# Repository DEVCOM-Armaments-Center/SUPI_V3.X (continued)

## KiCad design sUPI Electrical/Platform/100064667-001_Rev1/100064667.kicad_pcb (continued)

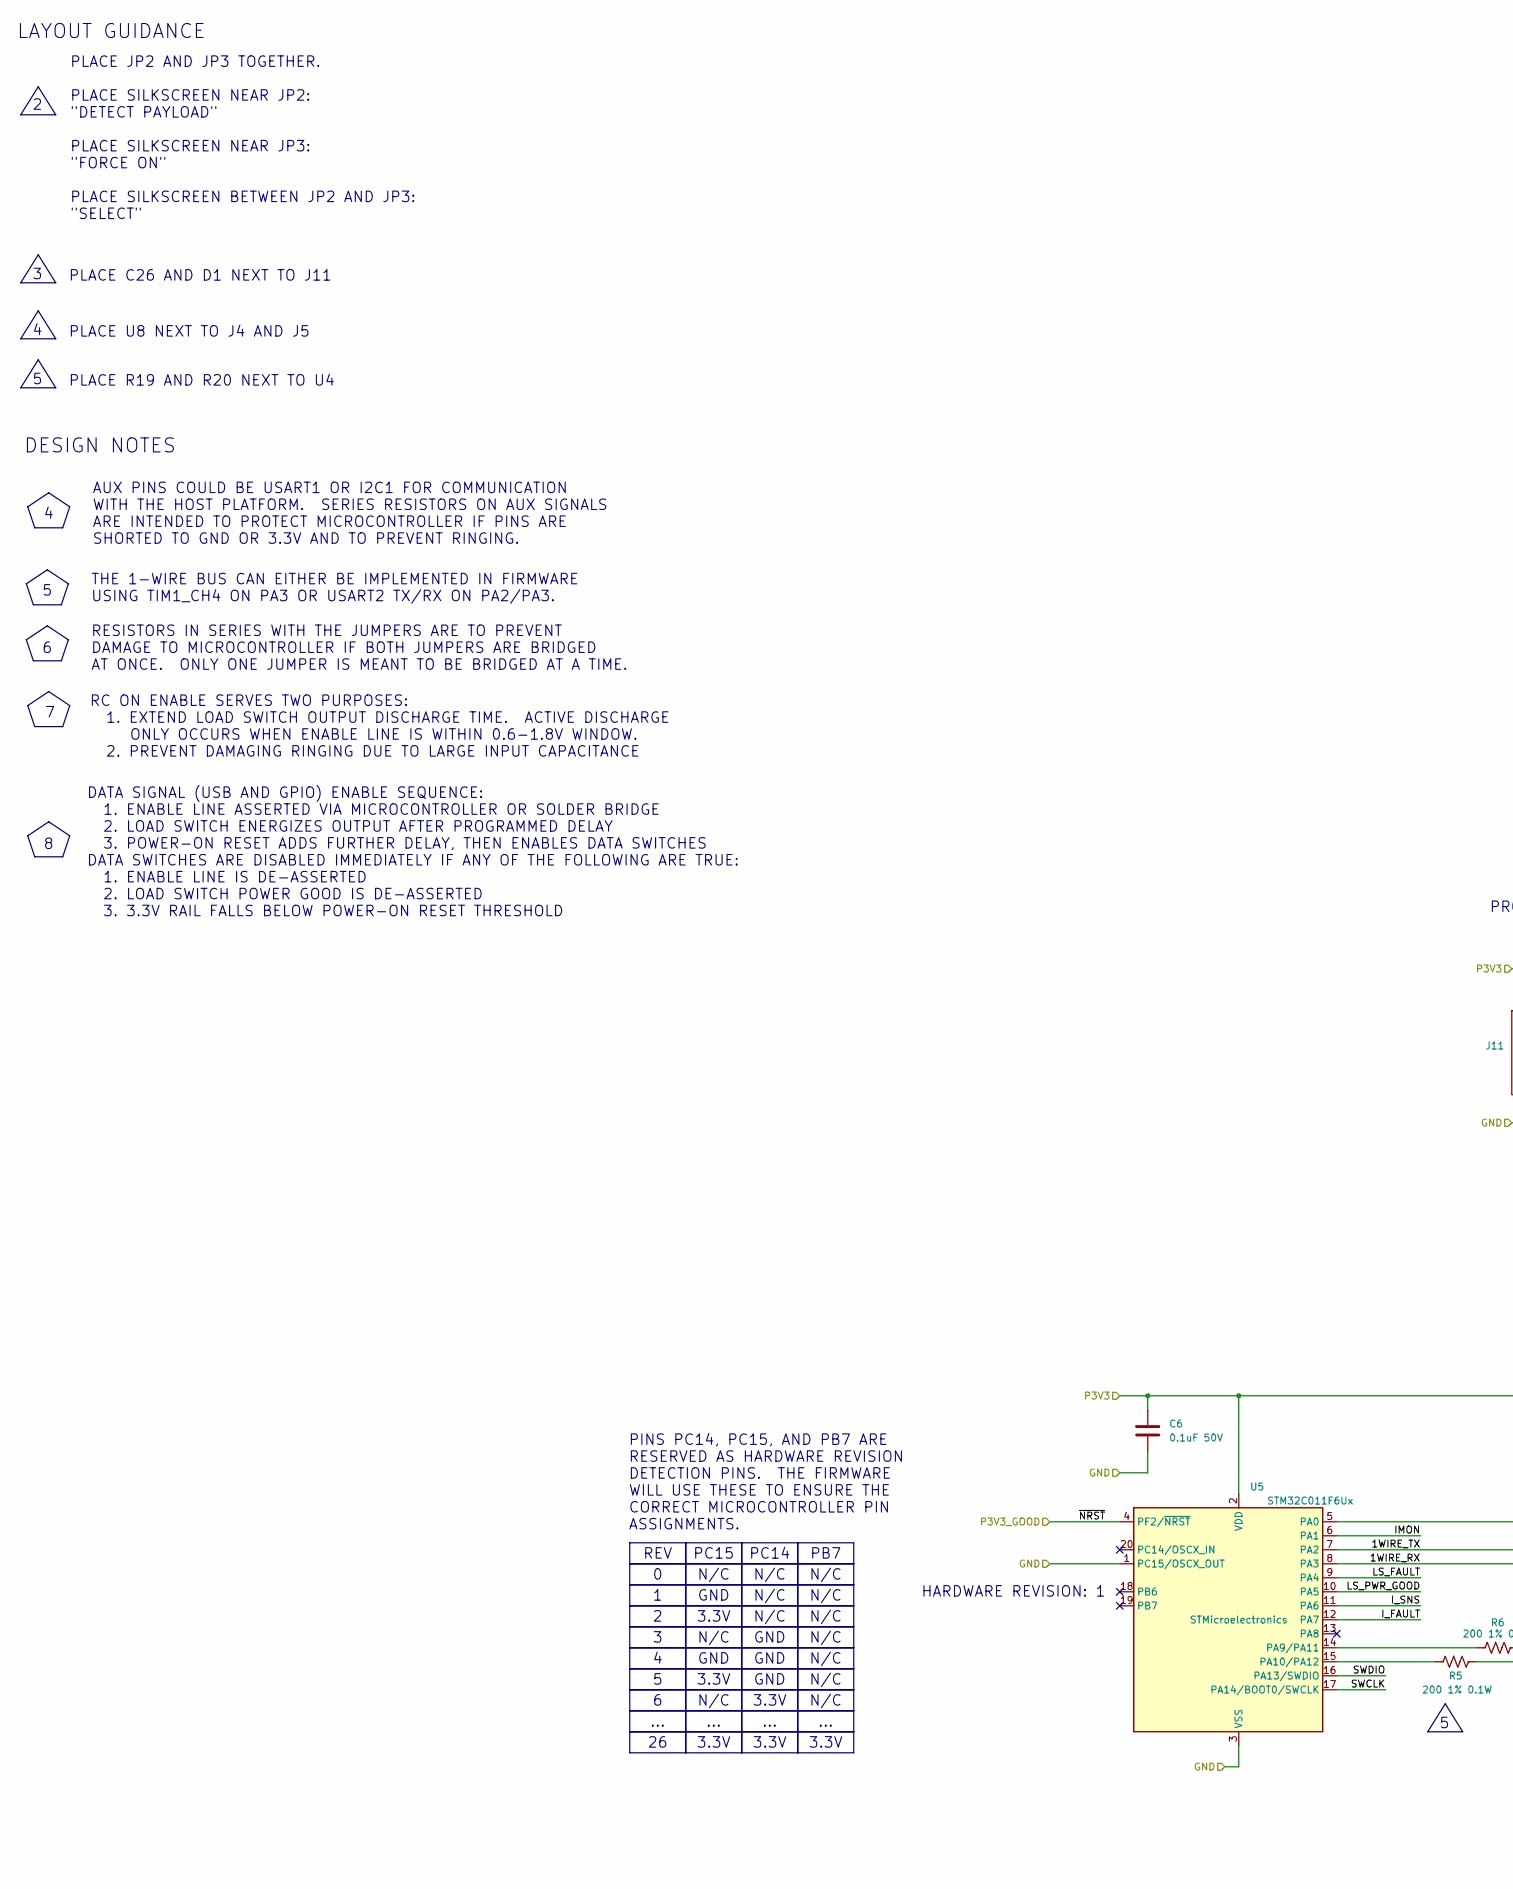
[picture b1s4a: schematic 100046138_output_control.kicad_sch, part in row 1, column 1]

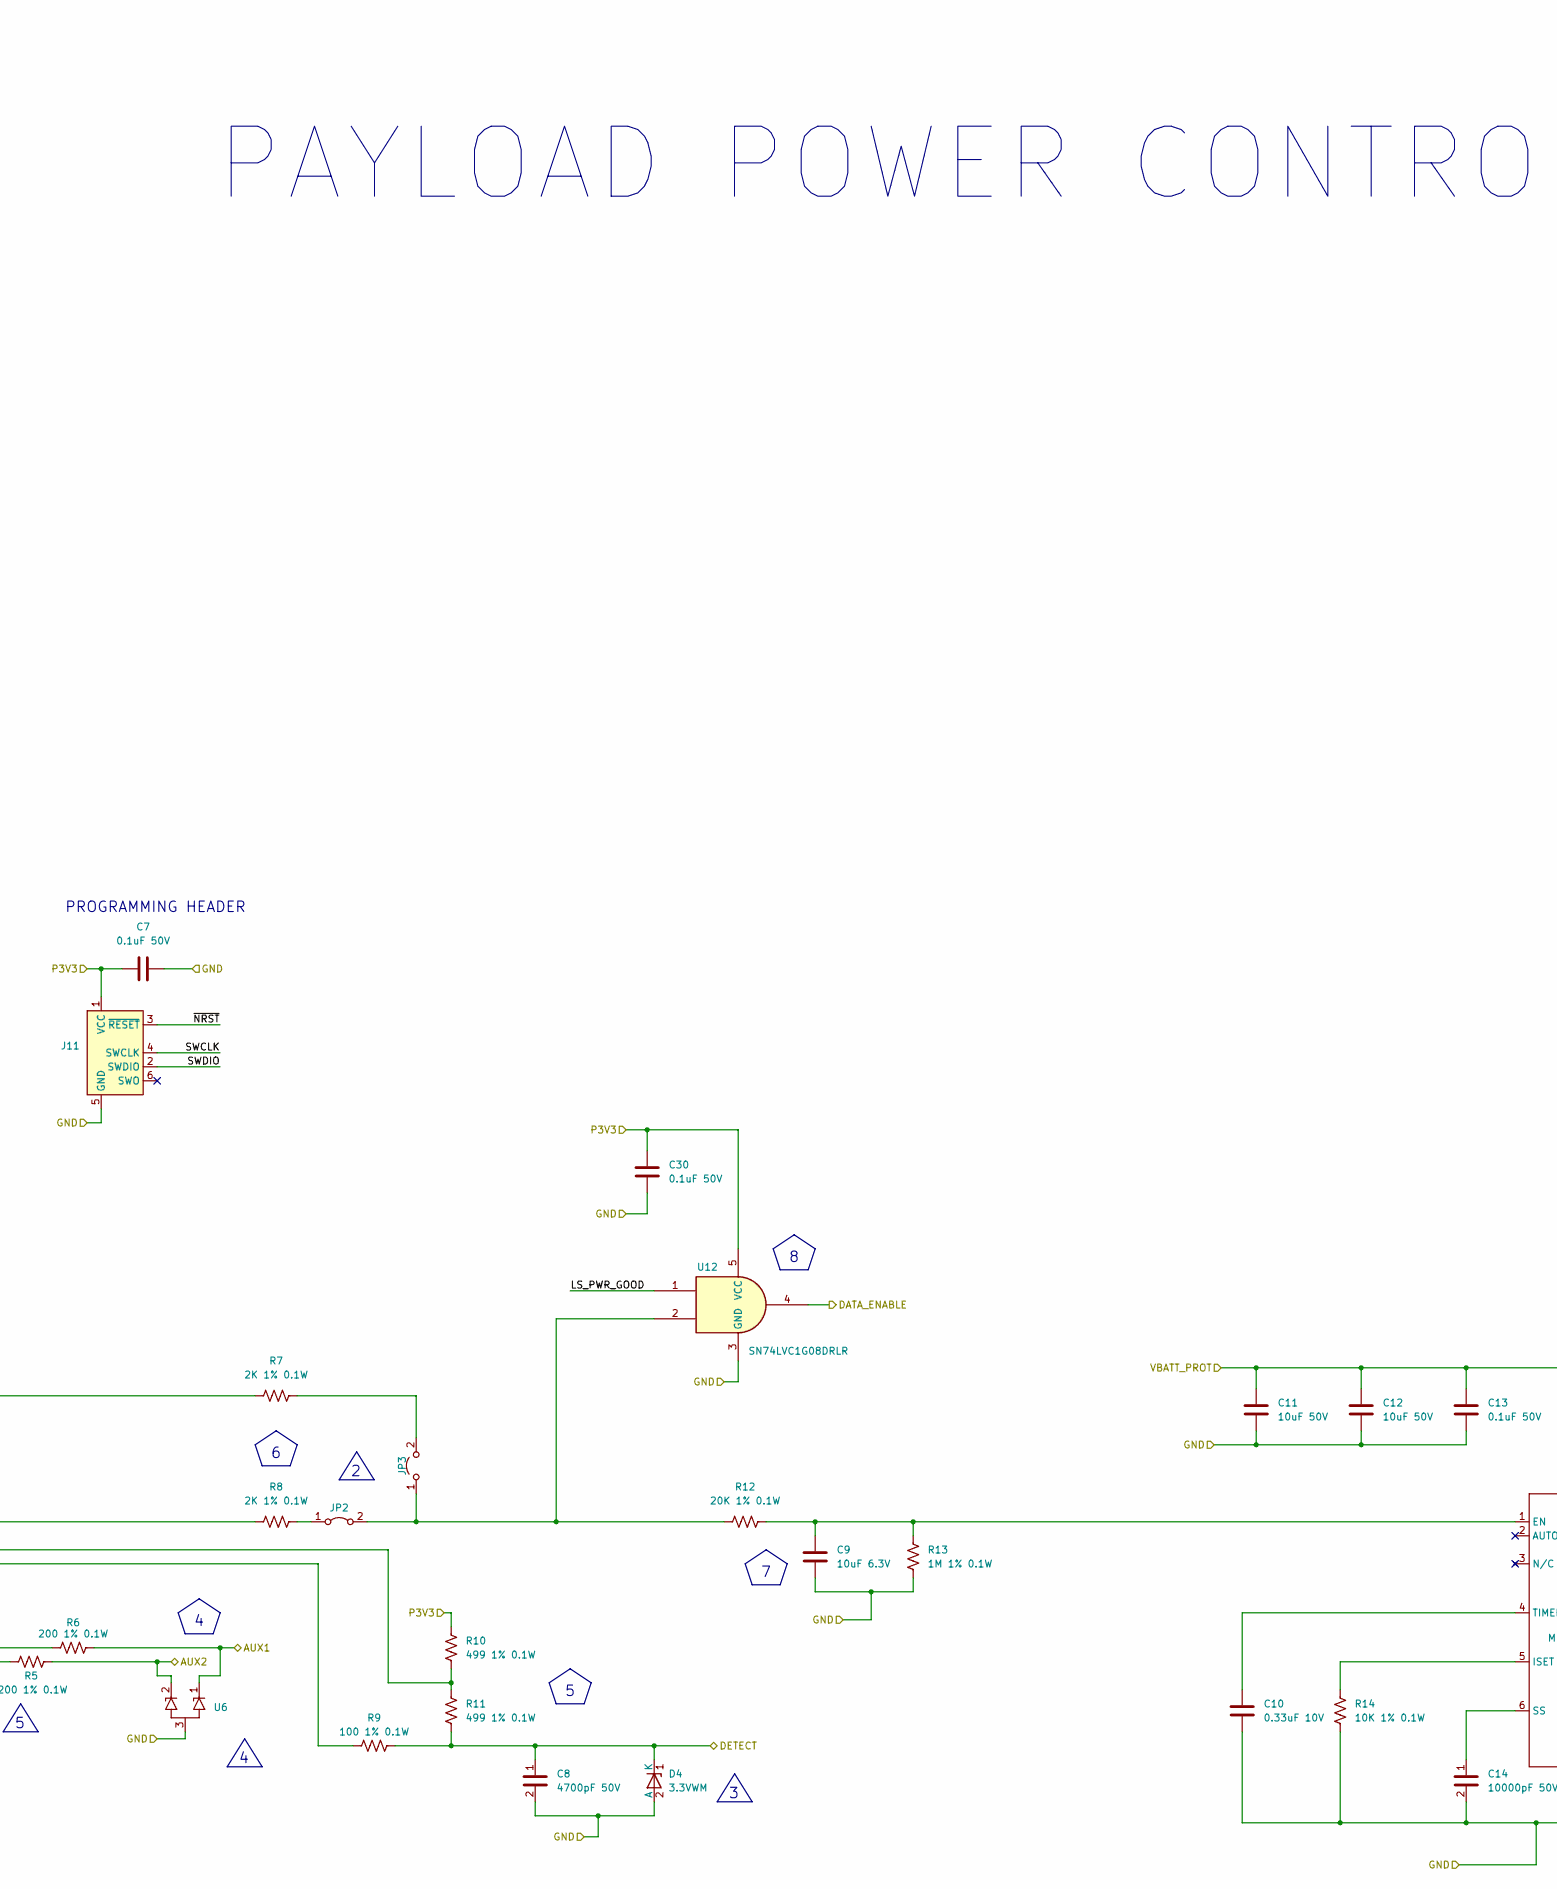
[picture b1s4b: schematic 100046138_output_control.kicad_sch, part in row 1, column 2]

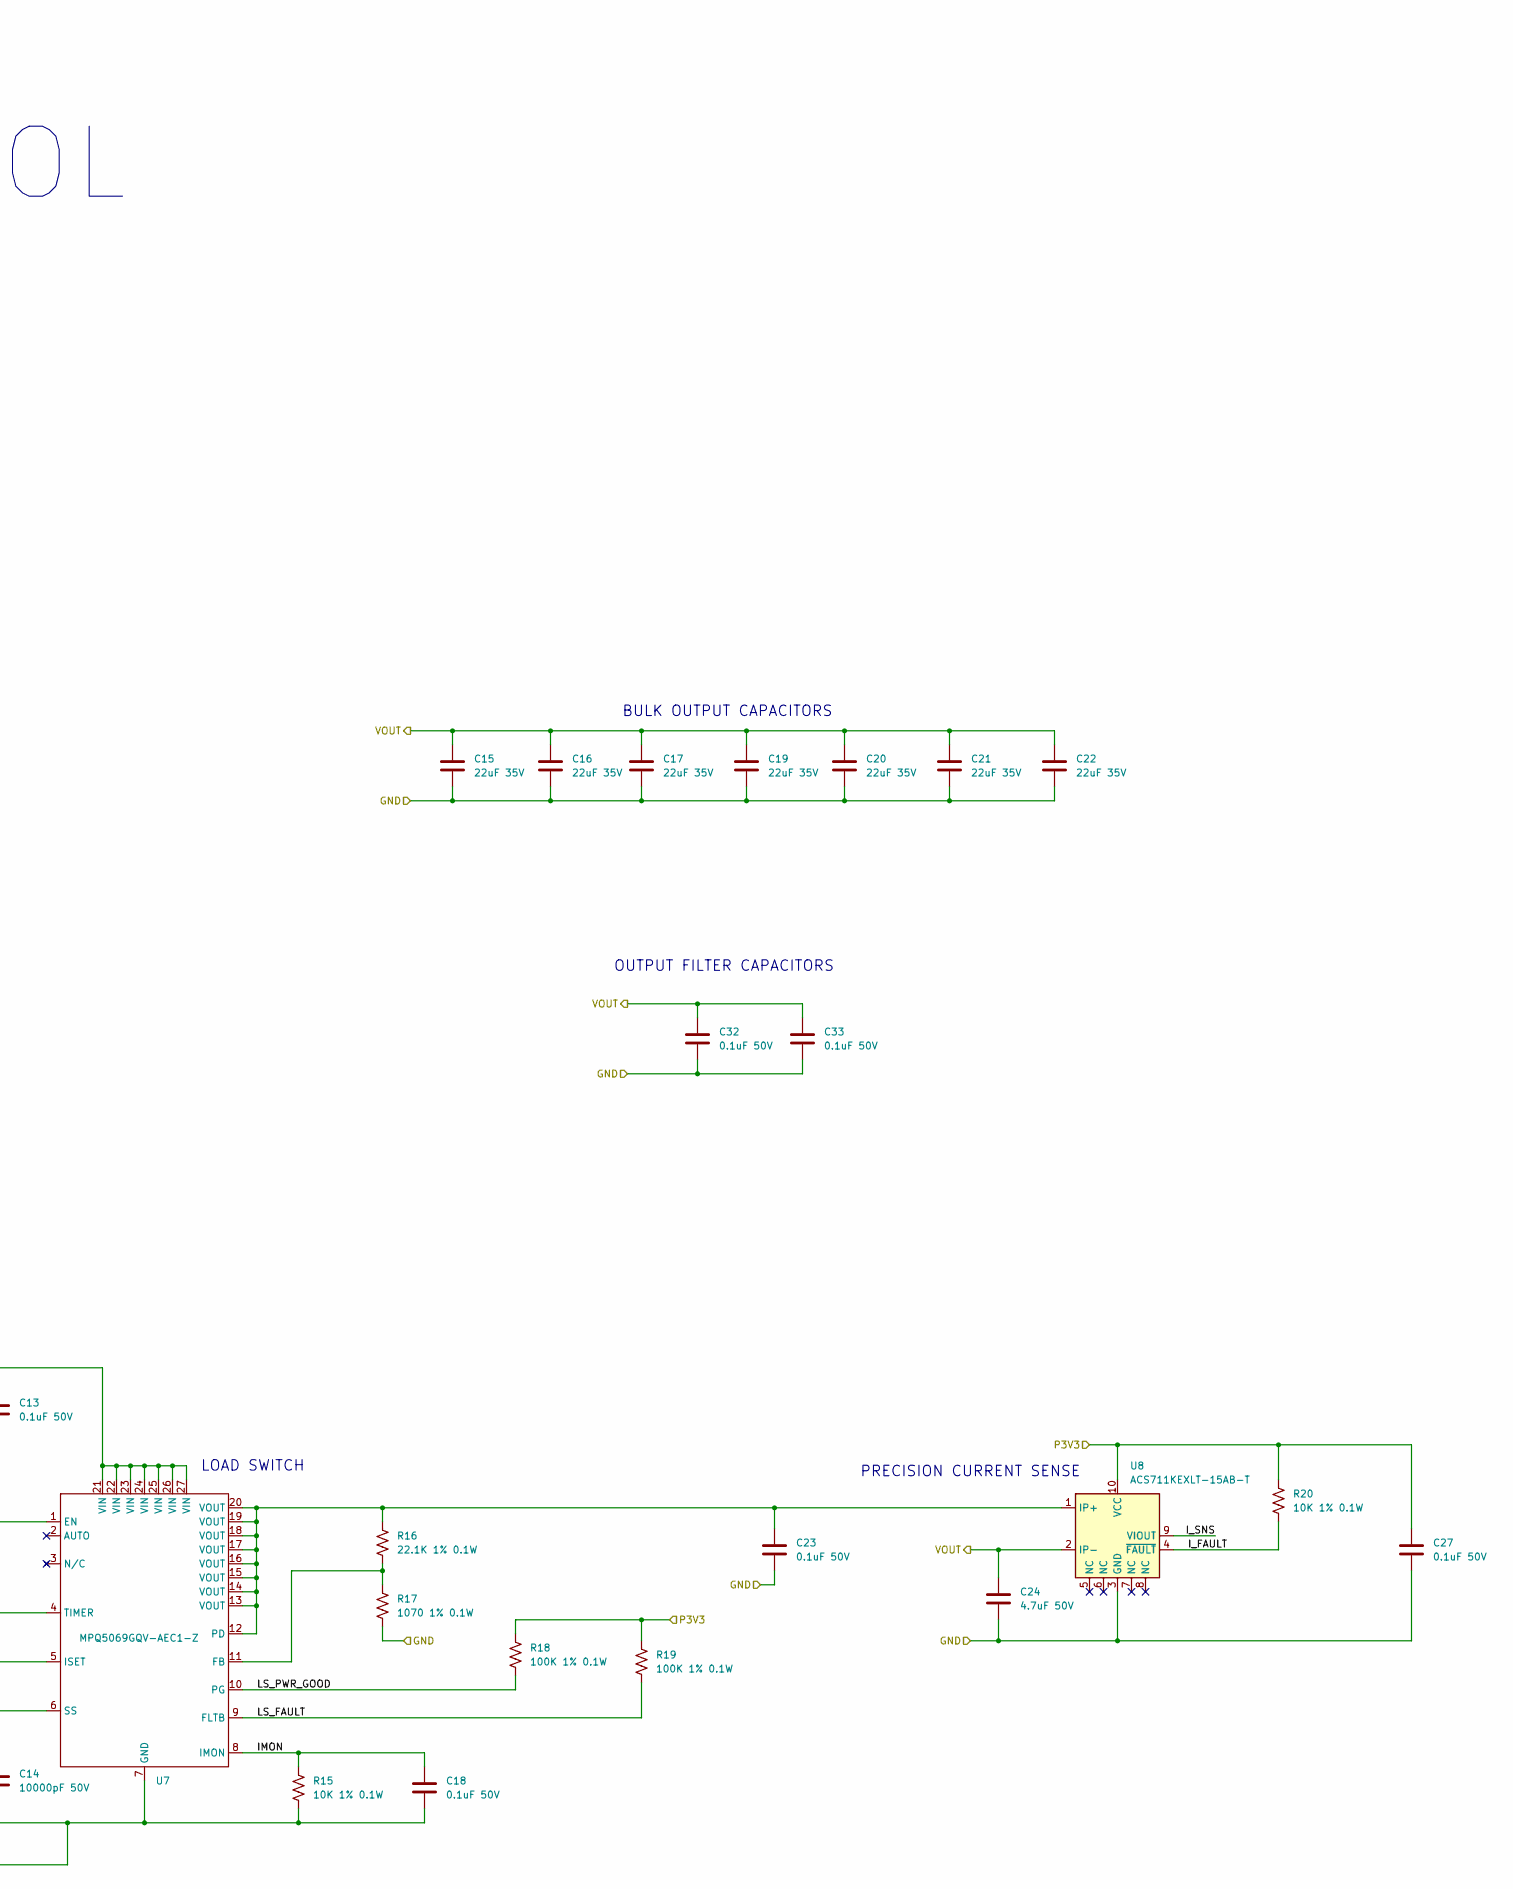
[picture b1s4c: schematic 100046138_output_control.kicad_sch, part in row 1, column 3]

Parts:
C6, C7, C13, C18, C23, C27, C30, C32, C33: 0.1uF 50V; C_0402_1005Metric; MPN GCM155R71H104ME02D
C8: 4700pF 50V; C_0402_1005Metric; MPN GCM155R71H472KA37J
C9: 10uF 6.3V; C_0402_1005Metric; MPN GRM155R60J106ME05D
C10: 0.33uF 10V; C_0402_1005Metric; MPN GRT155R61A334KE01J
C11, C12: 10uF 50V; C_0805_2012Metric; MPN GRM21BR61H106KE43L
C14: 10000pF 50V; C_0402_1005Metric; MPN GCM155R71H103KA55D
C15, C16, C17, C19, C20, C21, C22: 22uF 35V; C_0805_2012Metric; MPN C2012X5R1V226M125AC
C24: 4.7uF 50V; C_0805_2012Metric; MPN GRM21BZ71H475KE15L
D4: 3.3VWM; SOD-123FL; MPN SMF3.3
J11: Conn_ARM_SWD_TagConnect_TC2030-NL; Tag-Connect_TC2030-IDC-NL_2x03_P1.27mm_Vertical; MPN TC2030-CTX
JP2: Jumper_2_Bridged; SolderJumper-2_P1.3mm_Open_TrianglePad1.0x1.5mm
JP3: Jumper_2_Open; SolderJumper-2_P1.3mm_Open_TrianglePad1.0x1.5mm
R5, R6: 200 1% 0.1W; R_0402_1005Metric; MPN ERJ-2RKF2000X
R7, R8: 2K 1% 0.1W; R_0402_1005Metric; MPN ERJ-2RKF2001X
R9: 100 1% 0.1W; R_0402_1005Metric; MPN ERJ-2RKF1000X
R10, R11: 499 1% 0.1W; R_0402_1005Metric; MPN ERJ-2RKF4990X
R12: 20K 1% 0.1W; R_0402_1005Metric; MPN ERJ-2RKF2002X
R13: 1M 1% 0.1W; R_0402_1005Metric; MPN ERJ-2RKF1004X
R14, R15, R20: 10K 1% 0.1W; R_0402_1005Metric; MPN ERJ-U02F1002X
R16: 22.1K 1% 0.1W; R_0402_1005Metric; MPN ERJ-2RKF2212X
R17: 1070 1% 0.1W; R_0402_1005Metric; MPN ERJ-2RKF1071X
R18, R19: 100K 1% 0.1W; R_0402_1005Metric; MPN ERJ-2RKF1003X
U5: STM32C011F6Ux; ST_UFQFPN-20_3x3mm_P0.5mm; MPN STM32C011F6U6TR
U6: Diodes_DFN1006-3; MPN PESD5V0C2UM
U7: MPQ5069GQV-AEC1-Z; QFN-22_3_x_5mm; MPN MPQ5069GQV-AEC1-Z
U8: ACS711KEXLT-15AB-T; Allegro_QFN-12-10-1EP_3x3mm_P0.5mm; MPN ACS711KEXLT-15AB-T
U12: SN74LVC1G08DRLR; SOT-553 Texas Instruments DRL; MPN SN74LVC1G08DRLR

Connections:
/Block Diagram/AUX1: R6.1, U6.1 (K1); also elsewhere on the board
/Block Diagram/AUX2: R5.1, U6.2 (K2); also elsewhere on the board
/Block Diagram/Data Switches/DATA_ENABLE: U12.4; also elsewhere on the board
/Block Diagram/Data Switches/P3V3: C6.1, C7.2, C27.2, C30.1, J11.1 (VCC), R7.1, R10.1, R18.1, R19.1, R20.1, U5.2 (VDD), U8.10 (VCC), U12.5 (VCC); also elsewhere on the board
/Block Diagram/Payload Power Control/1WIRE_RX: R9.2, U5.8 (PA3)
/Block Diagram/Payload Power Control/1WIRE_TX: R10.2, R11.1, U5.7 (PA2)
/Block Diagram/Payload Power Control/DETECT: C8.1, D4.1 (K), R9.1, R11.2; also elsewhere on the board
/Block Diagram/Payload Power Control/IMON: C18.2, R15.1, U5.6 (PA1), U7.8 (IMON)
/Block Diagram/Payload Power Control/I_FAULT: R20.2, U5.12 (PA7), U8.4 (~FAULT)
/Block Diagram/Payload Power Control/I_SNS: U5.11 (PA6), U8.9 (VIOUT)
/Block Diagram/Payload Power Control/LS_FAULT: R19.2, U5.9 (PA4), U7.9 (FLTB)
/Block Diagram/Payload Power Control/LS_PWR_GOOD: R18.2, U5.10 (PA5), U7.10 (PG), U12.1
/Block Diagram/Payload Power Control/SWCLK: J11.4 (SWCLK), U5.17 (PA14/BOOT0/SWCLK)
/Block Diagram/Payload Power Control/SWDIO: J11.2 (SWDIO), U5.16 (PA13/SWDIO)
/Block Diagram/Payload Power Control/VBATT_PROT: C11.1, C12.1, C13.1, U7.21 (VIN), U7.22 (VIN), U7.23 (VIN), U7.24 (VIN), U7.25 (VIN), U7.26 (VIN), U7.27 (VIN); also elsewhere on the board
/Block Diagram/Payload Power Control/VOUT: C15.1, C16.1, C17.1, C19.1, C20.1, C21.1, C22.1, C24.1, C32.1, C33.1, U8.2 (IP-); also elsewhere on the board
/Block Diagram/Payload Power Control/~NRST: J11.3 (~RESET), U5.4 (PF2/~NRST); also elsewhere on the board
GND: C6.2, C7.1, C8.2, C9.2, C10.2, C11.2, C12.2, C13.2, C14.2, C15.2, C16.2, C17.2, C18.1, C19.2, C20.2, C21.2, C22.2, C23.2, C24.2, C27.1, C30.2, C32.2, C33.2, D4.2 (A), J11.5 (GND), R13.2, R14.2, R15.2, R17.2, U5.1 (PC15/OSCX_OUT), U5.3 (VSS), U6.3 (A), U7.7 (GND), U8.3 (GND), U12.3 (GND); also elsewhere on the board
unnamed: JP2.1 (A), R8.2
unnamed: JP2.2 (B), JP3.1 (A), R12.1, U12.2
unnamed: JP3.2 (B), R7.2
unnamed: R8.1, U5.5 (PA0)
unnamed: R6.2, U5.14 (PA9/PA11)
unnamed: R5.2, U5.15 (PA10/PA12)
unnamed: C9.1, R12.2, R13.1, U7.1 (EN)
unnamed: R16.2, R17.1, U7.11 (FB)
unnamed: R14.1, U7.5 (ISET)
unnamed: C23.1, R16.1, U7.12 (PD), U7.13 (VOUT), U7.14 (VOUT), U7.15 (VOUT), U7.16 (VOUT), U7.17 (VOUT), U7.18 (VOUT), U7.19 (VOUT), U7.20 (VOUT), U8.1 (IP+)
unnamed: C14.1, U7.6 (SS)
unnamed: C10.1, U7.4 (TIMER)

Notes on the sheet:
N/C
GND
3.3V
REV
PC14
...
PB7
PC15
DATA SIGNAL (USB AND GPIO) ENABLE SEQUENCE: 1. ENABLE LINE ASSERTED VIA MICROCONTROLLER OR SOLDER BRIDGE 2. LOAD SWITCH ENERGIZES OUTPUT AFTER PROGRAMMED DELAY 3. POWER-ON RESET ADDS FURTHER DELAY, THEN ENABLES DATA SWITCHES DATA SWITCHES ARE DISABLED IMMEDIATELY IF ANY OF THE FOLLOWING ARE TRUE: 1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
PLACE JP2 AND JP3 TOGETHER. PLACE SILKSCREEN NEAR JP2: "DETECT PAYLOAD" PLACE SILKSCREEN NEAR JP3: "FORCE ON" PLACE SILKSCREEN BETWEEN JP2 AND JP3: "SELECT"
RESISTORS IN SERIES WITH THE JUMPERS ARE TO PREVENT DAMAGE TO MICROCONTROLLER IF BOTH JUMPERS ARE BRIDGED AT ONCE. ONLY ONE JUMPER IS MEANT TO BE BRIDGED AT A TIME.
PRECISION CURRENT SENSE
RC ON ENABLE SERVES TWO PURPOSES: 1. EXTEND LOAD SWITCH OUTPUT DISCHARGE TIME. ACTIVE DISCHARGE ONLY OCCURS WHEN ENABLE LINE IS WITHIN 0.6-1.8V WINDOW. 2. PREVENT DAMAGING RINGING DUE TO LARGE INPUT CAPACITANCE
BULK OUTPUT CAPACITORS
OUTPUT FILTER CAPACITORS
LOAD SWITCH
DESIGN NOTES
PINS PC14, PC15, AND PB7 ARE RESERVED AS HARDWARE REVISION DETECTION PINS. THE FIRMWARE WILL USE THESE TO ENSURE THE CORRECT MICROCONTROLLER PIN ASSIGNMENTS.
THE 1-WIRE BUS CAN EITHER BE IMPLEMENTED IN FIRMWARE USING TIM1_CH4 ON PA3 OR USART2 TX/RX ON PA2/PA3.
PLACE R19 AND R20 NEXT TO U4
PROGRAMMING HEADER
PLACE U8 NEXT TO J4 AND J5
LAYOUT GUIDANCE
PLACE C26 AND D1 NEXT TO J11
AUX PINS COULD BE USART1 OR I2C1 FOR COMMUNICATION WITH THE HOST PLATFORM. SERIES RESISTORS ON AUX SIGNALS ARE INTENDED TO PROTECT MICROCONTROLLER IF PINS ARE SHORTED TO GND OR 3.3V AND TO PREVENT RINGING.
HARDWARE REVISION: 1
PAYLOAD POWER CONTROL

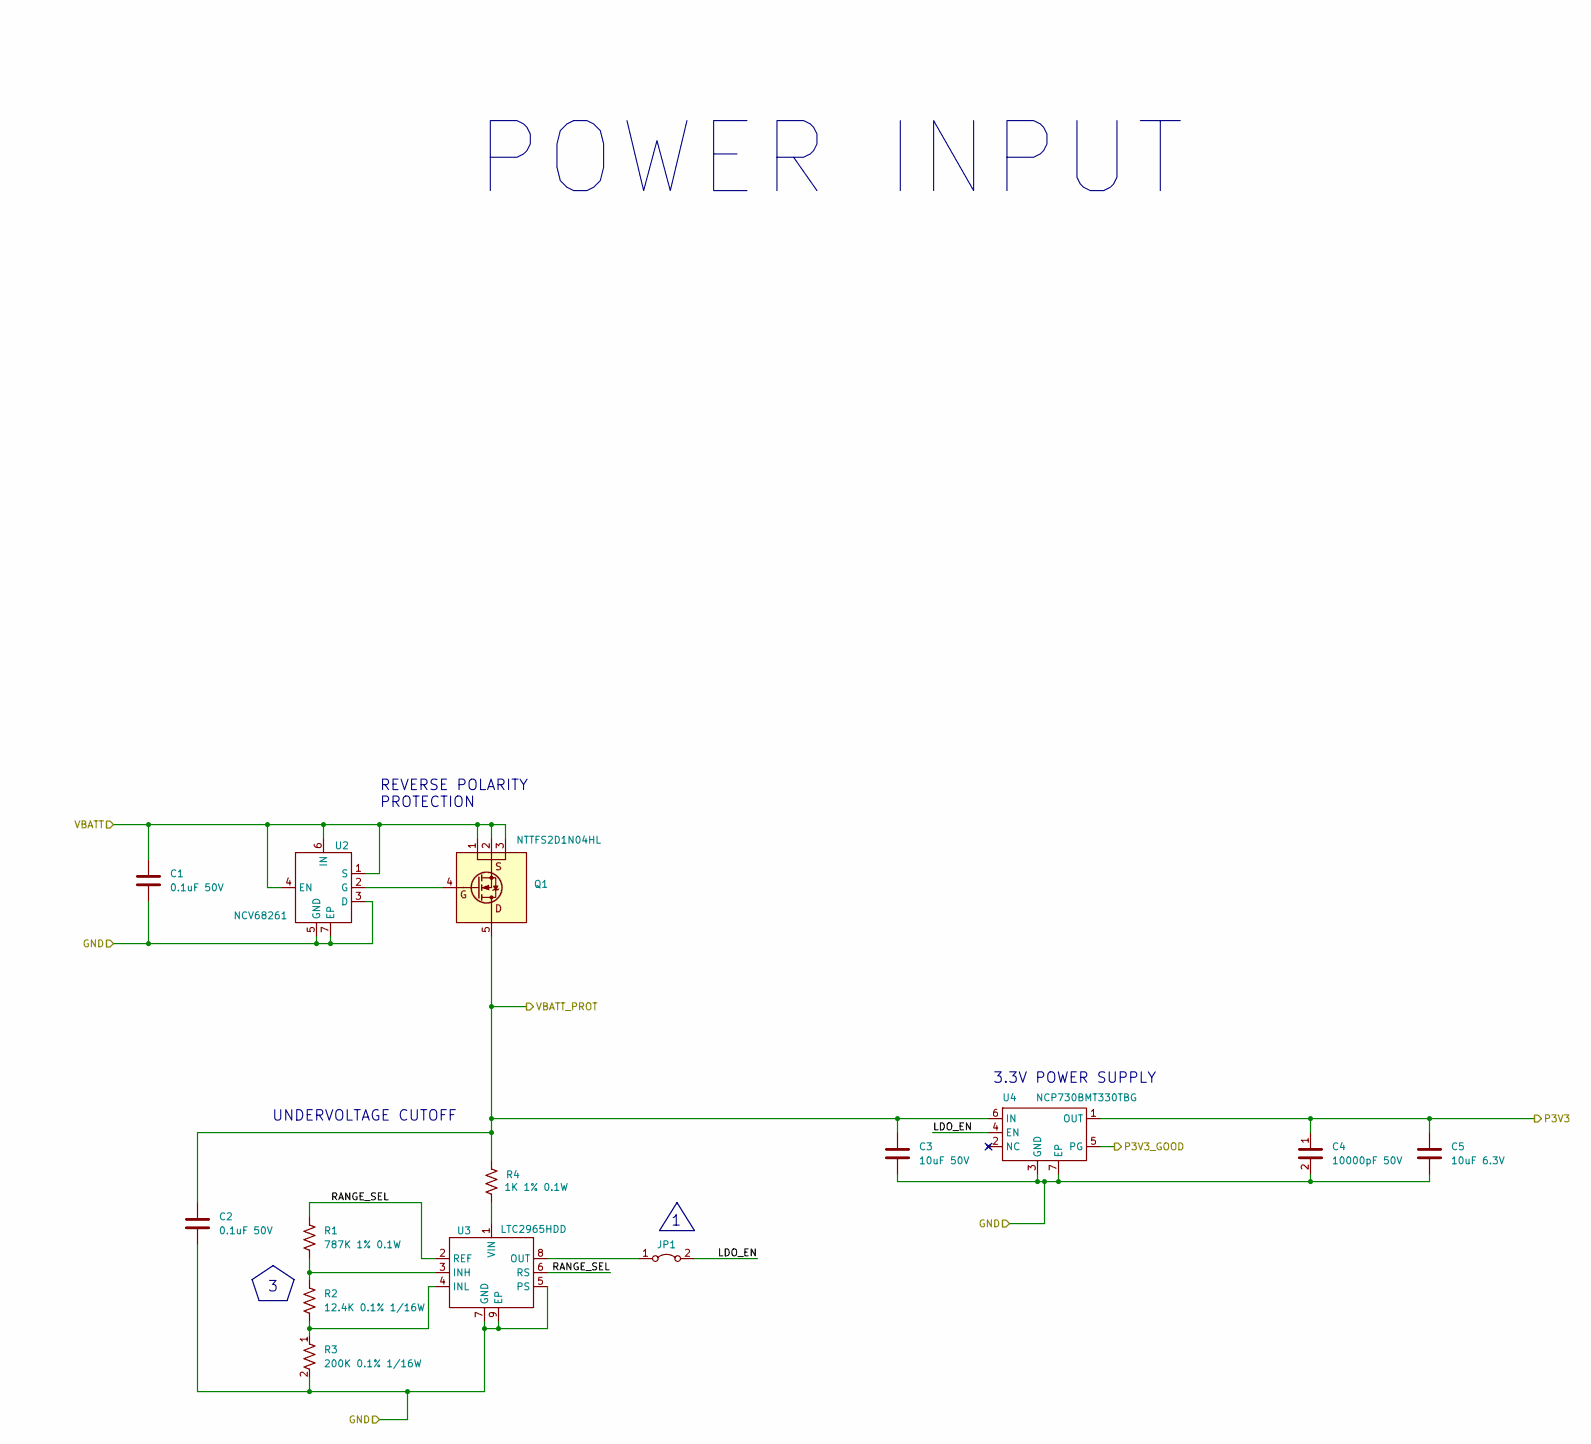
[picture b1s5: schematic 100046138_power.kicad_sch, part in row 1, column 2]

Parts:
C1, C2: 0.1uF 50V; C_0402_1005Metric; MPN GCM155R71H104ME02D
C3: 10uF 50V; C_0805_2012Metric; MPN GRM21BR61H106KE43L
C4: 10000pF 50V; C_0402_1005Metric; MPN GCM155R71H103KA55D
C5: 10uF 6.3V; C_0402_1005Metric; MPN GRM155R60J106ME05D
JP1: Jumper_2_Bridged; SolderJumper-2_P1.3mm_Open_TrianglePad1.0x1.5mm
Q1: NTTFS2D1N04HL; WDFN8_3.3_x_3.3_0.65mm_p; MPN NTTFS2D1N04HLTWG
R1: 787K 1% 0.1W; R_0402_1005Metric; MPN ERJ-2RKF7873X
R2: 12.4K 0.1% 1/16W; R_0402_1005Metric; MPN ERA-2ARB1242X
R3: 200K 0.1% 1/16W; R_0402_1005Metric; MPN RNCF0402BKE200K
R4: 1K 1% 0.1W; R_0402_1005Metric; MPN ERJ-2RKF1001X
U2: NCV68261; WDFNW6_2x2_0.65p_EP; MPN NCV68261MTWAITBG
U3: LTC2965HDD; DFN-8-1EP_3x3mm_P0.5mm_EP1.66x2.38mm; MPN LTC2965HDD#PBF
U4: NCP730BMT330TBG; WDFN6_2x2_0.65p_1.72x1.12mm_EP; MPN NCP730BMT330TBG

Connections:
/Block Diagram/Data Switches/P3V3: C4.1, C5.1, U4.1 (OUT); also elsewhere on the board
/Block Diagram/Payload Power Control/VBATT_PROT: C2.1, C3.1, Q1.5 (D), R4.1, U4.6 (IN); also elsewhere on the board
/Block Diagram/Payload Power Control/~NRST: U4.5 (PG); also elsewhere on the board
/Block Diagram/Power Input/LDO_EN: JP1.2 (B), U4.4 (EN)
/Block Diagram/Power Input/RANGE_SEL: R1.1, U3.2 (REF), U3.6 (RS)
/Block Diagram/VBATT: C1.1, Q1.1 (S), Q1.2 (S), Q1.3 (S), U2.1 (S), U2.4 (EN), U2.6 (IN); also elsewhere on the board
GND: C1.2, C2.2, C3.2, C4.2, C5.2, R3.2, U2.3 (D), U2.5 (GND), U2.7 (EP), U3.5 (PS), U3.7 (GND), U3.9 (EP), U4.3 (GND), U4.7 (EP); also elsewhere on the board
unnamed: JP1.1 (A), U3.8 (OUT)
unnamed: Q1.4 (G), U2.2 (G)
unnamed: R1.2, R2.1, U3.3 (INH)
unnamed: R2.2, R3.1, U3.4 (INL)
unnamed: R4.2, U3.1 (VIN)

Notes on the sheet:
3.3V POWER SUPPLY
RISING VOLTAGE: 20.4V FALLING VOLTAGE: 19.2V
DESIGN NOTES
UNDERVOLTAGE CUTOFF
PLACE SINKSCREEN TEXT NEAR JP1: "LO BATT CUTOFF"
POWER INPUT
LAYOUT GUIDANCE
REVERSE POLARITY PROTECTION

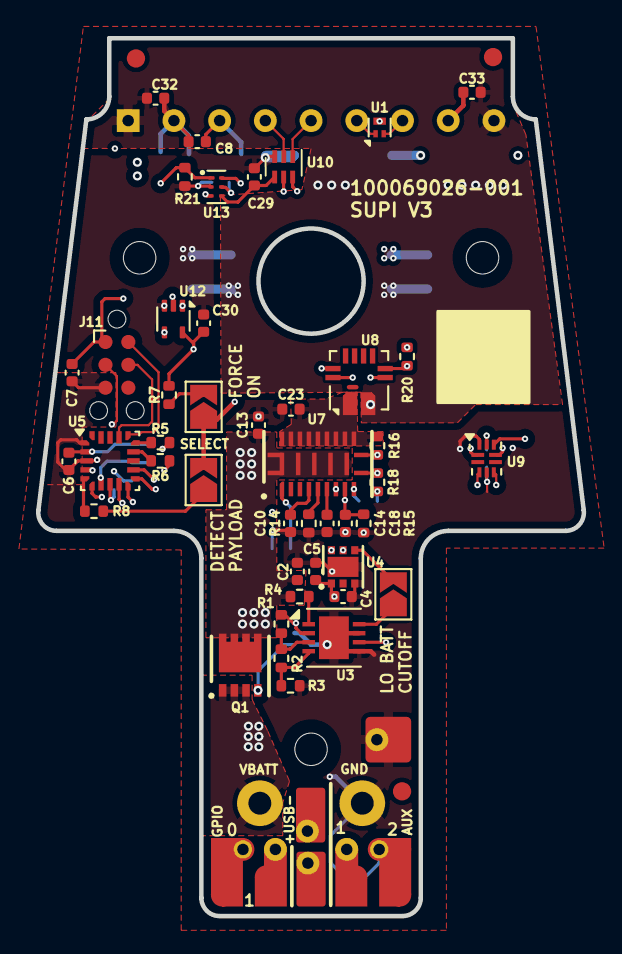
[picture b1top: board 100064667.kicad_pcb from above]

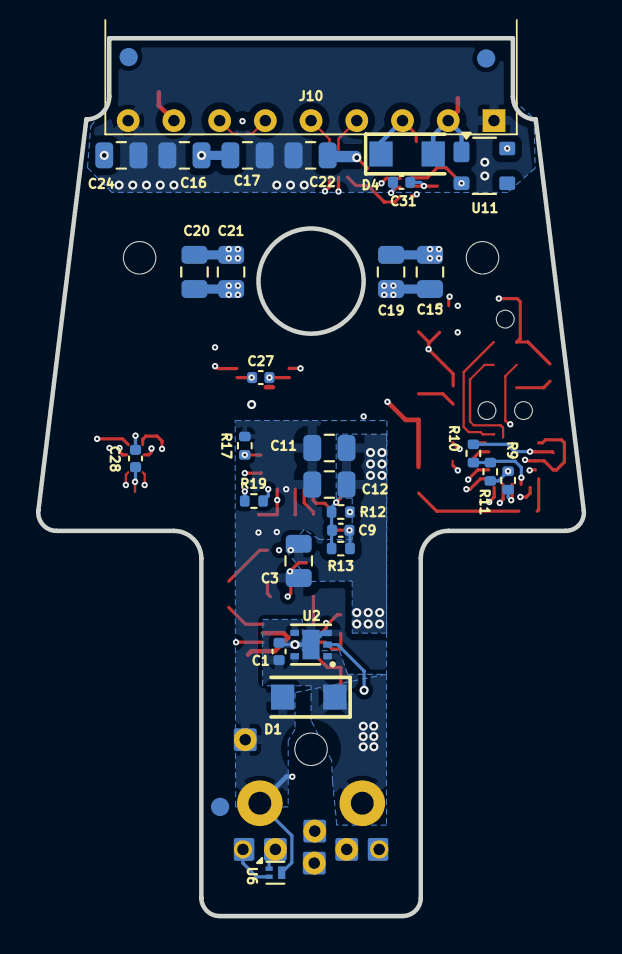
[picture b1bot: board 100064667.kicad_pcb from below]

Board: 8 copper layers, 30.3 x 48.8 mm, 91 parts (32 on the bottom side), 49 nets.

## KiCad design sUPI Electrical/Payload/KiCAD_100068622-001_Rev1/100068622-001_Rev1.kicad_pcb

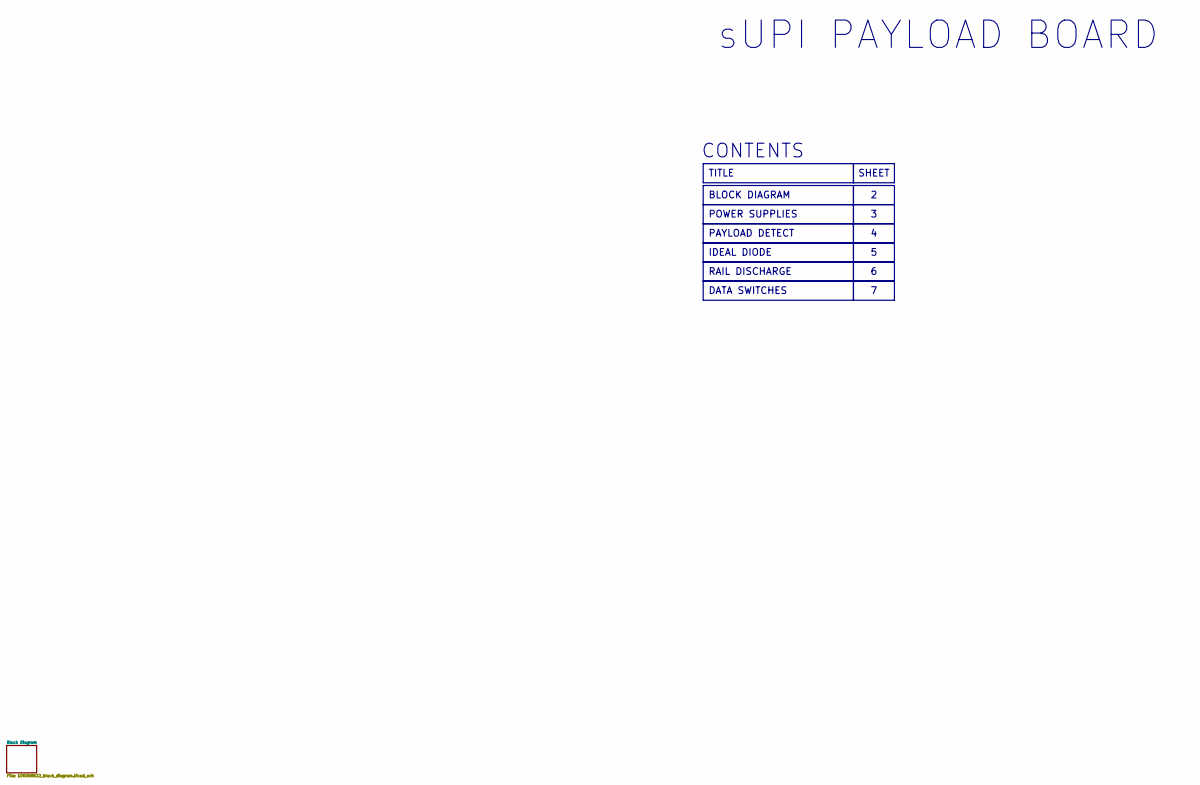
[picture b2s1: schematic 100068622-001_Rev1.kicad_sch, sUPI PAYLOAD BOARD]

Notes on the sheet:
SHEET
DATA SWITCHES
TITLE
PAYLOAD DETECT
BLOCK DIAGRAM
IDEAL DIODE
POWER SUPPLIES
RAIL DISCHARGE
sUPI PAYLOAD BOARD
CONTENTS
